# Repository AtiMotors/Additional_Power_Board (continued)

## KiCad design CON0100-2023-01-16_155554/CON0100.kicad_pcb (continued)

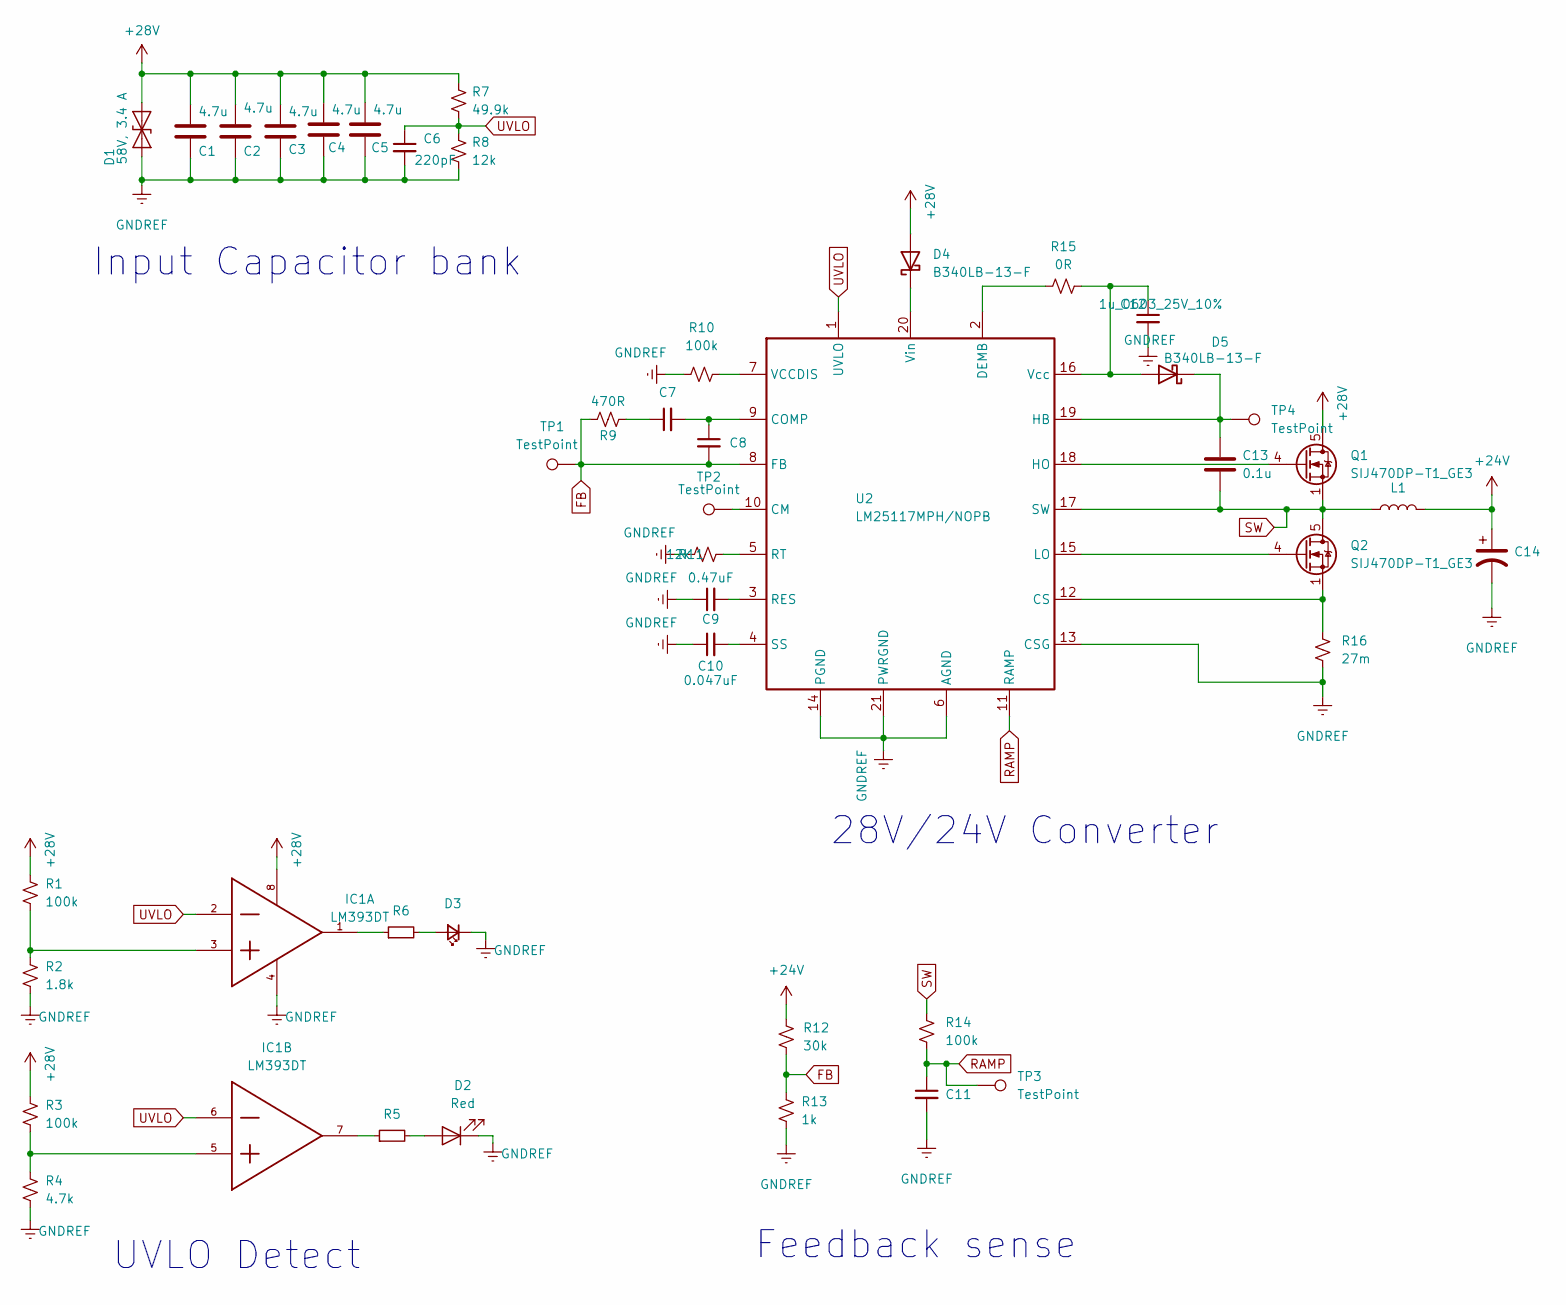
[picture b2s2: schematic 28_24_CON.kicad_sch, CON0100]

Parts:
C1, C2, C3, C4, C5: C_4.7u_1206_CL31B475KAHNNNE; R_1206_3216Metric_Pad1.42x1.75mm_HandSolder; MPN CL31B475KAHNNNE
C6: C_0603_220pF_50V_ECJ-1VC1H221J; C_0603_1608Metric_Pad1.08x0.95mm_HandSolder; MPN ECJ-1VC1H221J
C7: C_0.01uf_0603_50V_ECJ-1VB1H103K; C_0603_1608Metric_Pad1.08x0.95mm_HandSolder; MPN ECJ-1VB1H103K
C8: C_10pF_0603_GCM1885C1H100JA16D; C_0603_1608Metric_Pad1.08x0.95mm_HandSolder; MPN GCM1885C1H100JA16D
C9: C_0603_0.47uF_25V_CGA3E3X7R1E474K080AB; C_0603_1608Metric_Pad1.08x0.95mm_HandSolder; MPN CGA3E3X7R1E474K080AB
C10: C_0603_0.047uF_16V_10%_ECJ-1VB1C473K; C_0603_1608Metric_Pad1.08x0.95mm_HandSolder; MPN ECJ-1VB1C473K
C11: C_820pF_0603_50V_GCM1885C1H821JA16D; C_0603_1608Metric_Pad1.08x0.95mm_HandSolder; MPN GCM1885C1H821JA16D
C12: C_1uf_0603_GCJ188R71E105KA01D; C_0603_1608Metric_Pad1.08x0.95mm_HandSolder; MPN GCJ188R71E105KA01D
C13: C_0603_0.1u_50V_C0603C104K5RACAUTO; C_0603_1608Metric_Pad1.05x0.95mm_HandSolder; Voltage 50V; MPN C0603C104K5RACAUTO
C14: C_0.22uF_RAD_50V_20%; C_Elec_4x5.4; MPN UWP1HR22MCL1GB
D1: D_TVS_40V_ATV02W360B-HF; D_SOD-123F; MPN ATV02W360B-HF
D2: D_LED_0603_Red_150060RS75000; R_0603_1608Metric_Pad1.05x0.95mm_HandSolder; MPN 150060RS75000
D3: D_LED_0603_Green_150060GS75000; LED_0603_1608Metric_Pad1.05x0.95mm_HandSolder; MPN 150060GS75000
D4, D5: B340LB-13-F; D_SMC
IC1: LM393DT; SOIC8; MPN LM393DT
L1: L_22uH_12A_37mOhms_SMD_12.5mmx13.5mm; L_Bourns_SRP1245A; MPN SRP1265A-220M
Q1, Q2: SIJ470DP-T1_GE3; PowerPAK_SO-8_Single; MPN SIJ470DP-T1_GE3
R1, R3, R10: R_100k_0603_1/10W_CRGP0603F100K; R_0603_1608Metric_Pad0.98x0.95mm_HandSolder; MPN ERJ-3EKF1003V
R2: R_1.8k_0603_ERJ-3EKF1801V; R_0603_1608Metric_Pad0.98x0.95mm_HandSolder; MPN ERJ-3EKF1801V
R4: R_4.7k_0603_ERJ-3GEYJ472V; R_0603_1608Metric_Pad0.98x0.95mm_HandSolder; MPN ERJ-3GEYJ472V
R5, R6: R_3.3k_0603_ERJ-PA3F3301V; R_0603_1608Metric_Pad0.98x0.95mm_HandSolder; MPN ERJ-PA3F3301V
R7: R_49.9k_0603_ERJ3EKF4992V; R_0603_1608Metric_Pad0.98x0.95mm_HandSolder; MPN ERJ-3EKF4992V
R8, R11: R_12k_0603_ERJ3EKF1202V; R_0603_1608Metric_Pad0.98x0.95mm_HandSolder; MPN ERJ-3EKF1202V
R9: R_470R_0603_ERJ-3EKF4700V; R_0603_1608Metric_Pad0.98x0.95mm_HandSolder; MPN ERJ-3EKF4700V
R12: R_30k_0603_ERJ-PB3B3002V; R_0603_1608Metric_Pad0.98x0.95mm_HandSolder; MPN ERJ-PB6B3002V
R13: R_1k_0603_ERJ-3EKF1001V; R_0603_1608Metric_Pad0.98x0.95mm_HandSolder; MPN 3EKF1001V
R14: R_100k_0603_0.1%_ERA3APB104V; R_0603_1608Metric_Pad1.05x0.95mm_HandSolder; MPN ERA3APB104V
R15: R_0R_0603_ERJ-3GEY0R00V; R_0603_1608Metric_Pad0.98x0.95mm_HandSolder; MPN ERJ-3GEY0R00V
R16: R_27mOhms_0805_ERJ-6BWFR027V; R_0805_2012Metric_Pad1.20x1.40mm_HandSolder; MPN ERJ-6BWFR027V
TP1, TP2, TP3, TP4: TestPoint; TestPoint_Pad_D1.0mm
U2: LM25117MPH/NOPB; SOP65P640X110-21N

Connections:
+24V: C14.1, L1.2, R12.1; also elsewhere on the board
+28V: C1.1, C2.1, C3.1, C4.1, C5.1, D1.2 (A2), D4.2 (A), IC1.8, Q1.5 (D), R1.1, R3.1, R7.1; also elsewhere on the board
FB: C8.2, R9.1, R12.2, R13.1, TP1.1, U2.8 (FB)
GNDREF: C1.2, C2.2, C3.2, C4.2, C5.2, C6.2, C9.1, C10.1, C11.2, C12.2, C14.2, D1.1 (A1), D2.1 (K), D3.1 (K), IC1.4, R2.2, R4.2, R8.2, R10.1, R11.1, R13.2, R16.2, U2.6 (AGND), U2.13 (CSG), U2.14 (PGND), U2.21 (PWRGND); also elsewhere on the board
unnamed: C7.1, R9.2
unnamed: C7.2, C8.1, U2.9 (COMP)
unnamed: C9.2, U2.3 (RES)
unnamed: C10.2, U2.4 (SS)
unnamed: C13.1, D5.1 (K), TP4.1, U2.19 (HB)
unnamed: D2.2 (A), R5.2
unnamed: D3.2 (A), R6.2
unnamed: D4.1 (K), U2.20 (Vin)
unnamed: C12.1, D5.2 (A), R15.2, U2.16 (Vcc)
unnamed: IC1.1, R6.1
unnamed: IC1.3, R1.2, R2.1
unnamed: IC1.5, R3.2, R4.1
unnamed: IC1.7, R5.1
unnamed: Q2.1 (S), Q2.2 (S), Q2.3 (S), R16.1, U2.12 (CS)
unnamed: R10.2, U2.7 (VCCDIS)
unnamed: R11.2, U2.5 (RT)
unnamed: R15.1, U2.2 (DEMB)
unnamed: TP2.1, U2.10 (CM)
unnamed: Q2.4 (G), U2.15 (LO)
unnamed: Q1.4 (G), U2.18 (HO)
RAMP: C11.1, R14.2, TP3.1, U2.11 (RAMP)
SW: C13.2, L1.1, Q1.1 (S), Q1.2 (S), Q1.3 (S), Q2.5 (D), R14.1, U2.17 (SW)
UVLO: C6.1, IC1.2, IC1.6, R7.2, R8.1, U2.1 (UVLO)

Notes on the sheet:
UVLO Detect
Feedback sense
28V/24V Converter
Input Capacitor bank

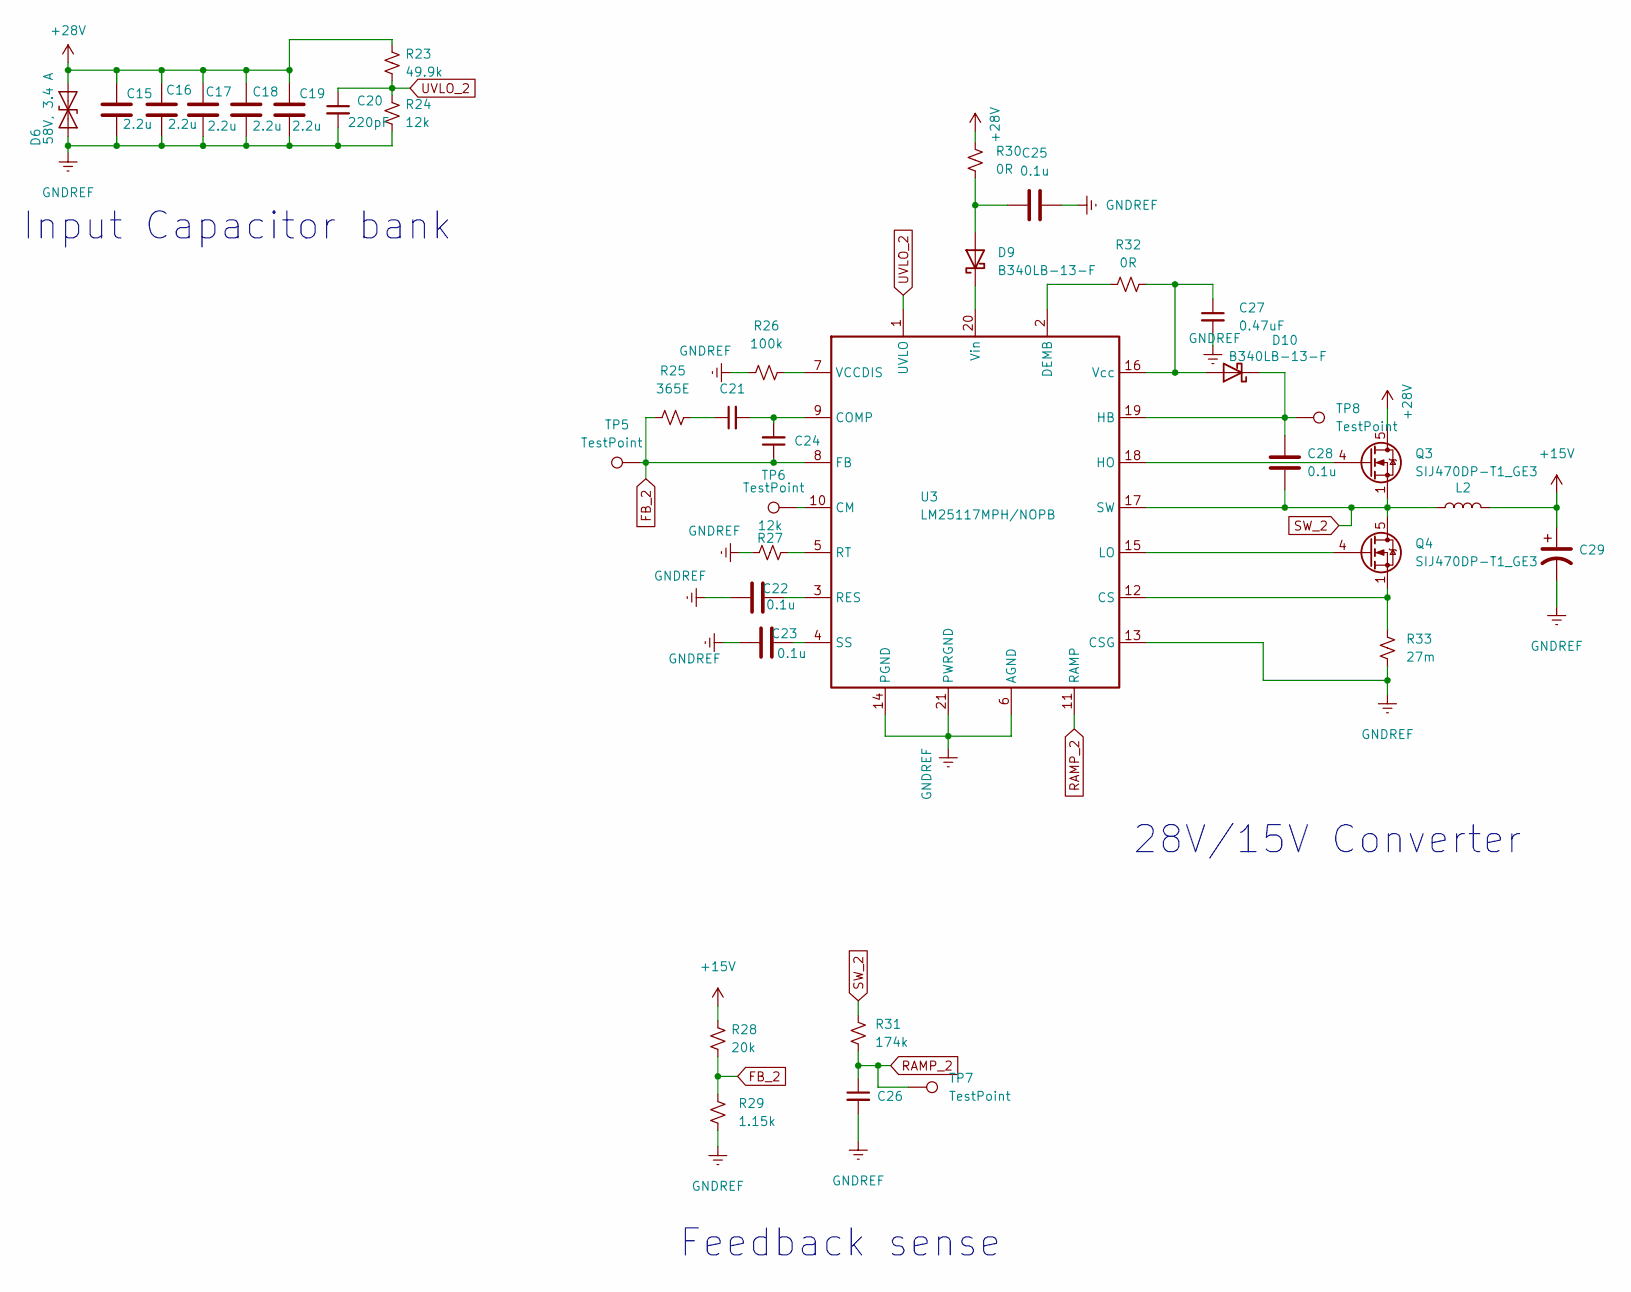
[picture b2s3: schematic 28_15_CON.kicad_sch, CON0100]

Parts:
C15, C16, C17, C19: C_2.2u_1210_C1210F225K5RACAUTO; C_1210_3225Metric_Pad1.33x2.70mm_HandSolder; MPN C1210F225K5RACAUTO
C18: C_1210_3225Metric_Pad1.33x2.70mm_HandSolder; MPN C1210F225K5RACAUTO
C20: C_0603_220pF_50V_ECJ-1VC1H221J; C_0603_1608Metric_Pad1.08x0.95mm_HandSolder; MPN ECJ-1VC1H221J
C21: C_4700pF_0805_CL21C472JAFNNNE; C_0805_2012Metric_Pad1.18x1.45mm_HandSolder; MPN CL21C472JAFNNNE
C22, C23, C25, C28: C_0603_0.1u_50V_C0603C104K5RACAUTO; C_0603_1608Metric_Pad1.05x0.95mm_HandSolder; Voltage 50V; MPN C0603C104K5RACAUTO
C24: C_150pF_0805_08055A151J4T4A; C_0805_2012Metric_Pad1.18x1.45mm_HandSolder; MPN 08055A151J4T4A
C26: C_820pF_0603_50V_GCM1885C1H821JA16D; C_0603_1608Metric_Pad1.08x0.95mm_HandSolder; MPN GCM1885C1H821JA16D
C27: C_0603_0.47uF_25V_CGA3E3X7R1E474K080AB; C_0603_1608Metric_Pad1.08x0.95mm_HandSolder; MPN CGA3E3X7R1E474K080AB
C29: C_0.22uF_RAD_50V_20%; C_Elec_4x5.4; MPN UWP1HR22MCL1GB
D6: D_TVS_40V_ATV02W360B-HF; D_SOD-123F; MPN ATV02W360B-HF
D9, D10: B340LB-13-F; D_SMC
L2: L_33uH_3A_60mOhms_SMD_12.5mmx12.5mm; L_Bourns_SRR1260; MPN SRR1260-330M
Q3, Q4: SIJ470DP-T1_GE3; PowerPAK_SO-8_Single; MPN SIJ470DP-T1_GE3
R23: MPN ERJ-3EKF4992V
R24, R27: R_12k_0603_ERJ3EKF1202V; R_0603_1608Metric_Pad0.98x0.95mm_HandSolder; MPN ERJ-3EKF1202V
R25: R_365R_0603_ERA-3AEB3650V; R_0603_1608Metric_Pad0.98x0.95mm_HandSolder; MPN 3AEB3650V
R26: R_100k_0603_1/10W_CRGP0603F100K; R_0603_1608Metric_Pad0.98x0.95mm_HandSolder; MPN ERJ-3EKF1003V
R28: R_20k_0603_ERJ-3EKF2002V; R_0603_1608Metric_Pad0.98x0.95mm_HandSolder; MPN ERJ-3EKF2002V
R29: R_1.15k_0603_ERJ-3EKF1151V; R_0603_1608Metric_Pad0.98x0.95mm_HandSolder; MPN ERJ-3EKF1151V
R30, R32: R_0R_0603_ERJ-3GEY0R00V; R_0603_1608Metric_Pad0.98x0.95mm_HandSolder; MPN ERJ-3GEY0R00V
R31: R_174k_0603_ERJ-3EKF1743V; R_0603_1608Metric_Pad0.98x0.95mm_HandSolder; MPN ERJ-3EKF1743V
R33: R_27mOhms_0805_ERJ-6BWFR027V; R_0805_2012Metric_Pad1.20x1.40mm_HandSolder; MPN ERJ-6BWFR027V
TP5, TP6, TP7, TP8: TestPoint; TestPoint_Pad_D1.0mm
U3: LM25117MPH/NOPB; SOP65P640X110-21N

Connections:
+15V: C29.1, L2.2, R28.1; also elsewhere on the board
+28V: C15.1, C16.1, C17.1, C18.1, C19.1, D6.2 (A2), Q3.5 (D), R23.1, R30.2; also elsewhere on the board
FB_2: C24.1, R25.1, R28.2, R29.1, TP5.1, U3.8 (FB)
GNDREF: C15.2, C16.2, C17.2, C18.2, C19.2, C20.2, C22.1, C23.1, C25.2, C26.2, C27.2, C29.2, D6.1 (A1), R24.2, R26.1, R27.1, R29.2, R33.2, U3.6 (AGND), U3.13 (CSG), U3.14 (PGND), U3.21 (PWRGND); also elsewhere on the board
unnamed: C21.1, R25.2
unnamed: C21.2, C24.2, U3.9 (COMP)
unnamed: C22.2, U3.3 (RES)
unnamed: C23.2, U3.4 (SS)
unnamed: C25.1, D9.2 (A), R30.1
unnamed: C27.1, D10.2 (A), R32.2, U3.16 (Vcc)
unnamed: C28.1, D10.1 (K), TP8.1, U3.19 (HB)
unnamed: D9.1 (K), U3.20 (Vin)
unnamed: Q3.4 (G), U3.18 (HO)
unnamed: Q4.1 (S), Q4.2 (S), Q4.3 (S), R33.1, U3.12 (CS)
unnamed: Q4.4 (G), U3.15 (LO)
unnamed: R26.2, U3.7 (VCCDIS)
unnamed: R27.2, U3.5 (RT)
unnamed: R32.1, U3.2 (DEMB)
unnamed: TP6.1, U3.10 (CM)
RAMP_2: C26.1, R31.2, TP7.1, U3.11 (RAMP)
SW_2: C28.2, L2.1, Q3.1 (S), Q3.2 (S), Q3.3 (S), Q4.5 (D), R31.1, U3.17 (SW)
UVLO_2: C20.1, R23.2, R24.1, U3.1 (UVLO); also elsewhere on the board

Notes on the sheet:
28V/15V Converter
Feedback sense
Input Capacitor bank

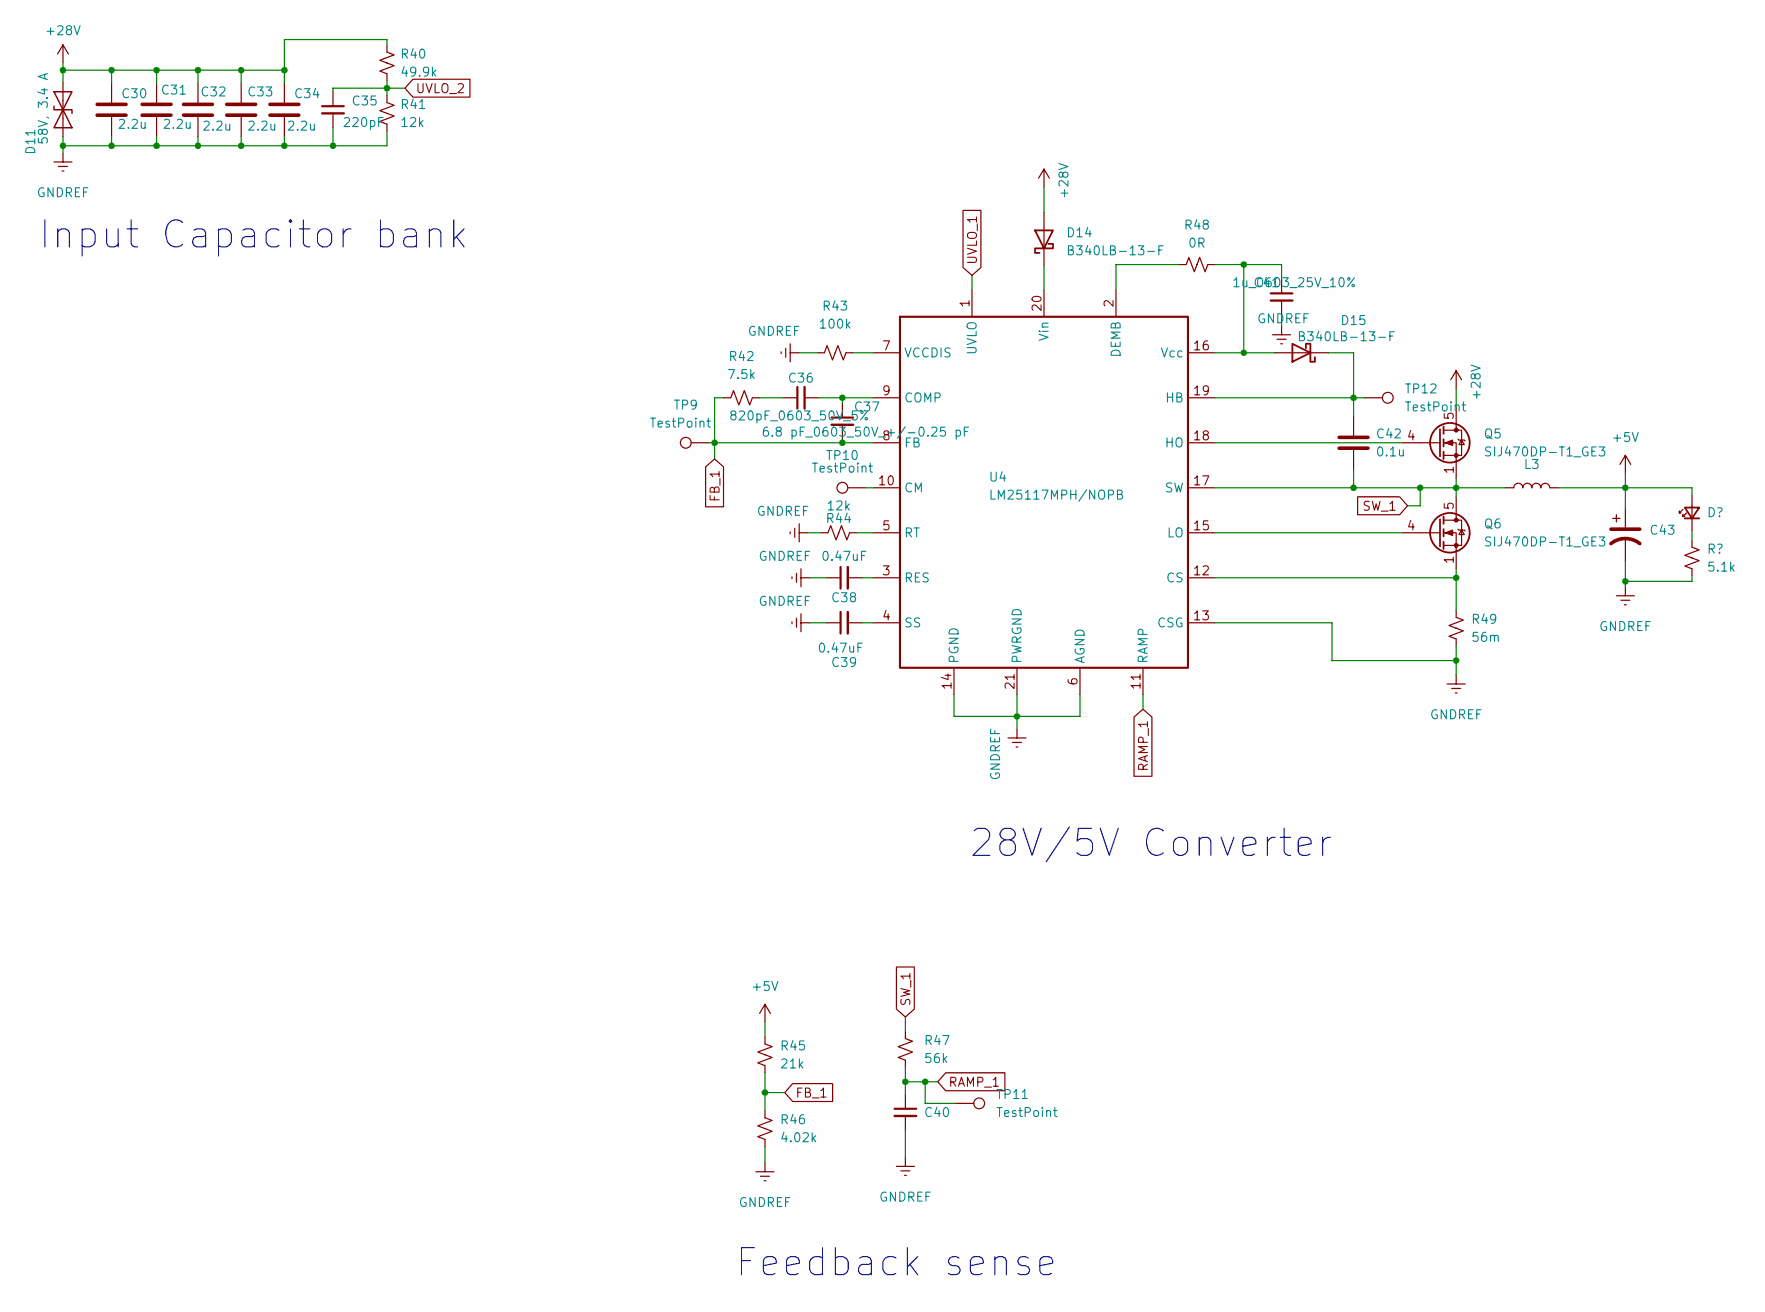
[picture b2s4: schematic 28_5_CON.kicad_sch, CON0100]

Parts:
C30, C31, C32, C33, C34: C_2.2u_1210_C1210F225K5RACAUTO; C_1210_3225Metric_Pad1.33x2.70mm_HandSolder; MPN C1210F225K5RACAUTO
C35: C_0603_220pF_50V_ECJ-1VC1H221J; C_0603_1608Metric_Pad1.08x0.95mm_HandSolder; MPN ECJ-1VC1H221J
C36, C40: C_820pF_0603_50V_GCM1885C1H821JA16D; C_0603_1608Metric_Pad1.08x0.95mm_HandSolder; MPN GCM1885C1H821JA16D
C37: C_6.8pF_0603_CL10C6R8CB8NNNC; C_0603_1608Metric_Pad1.08x0.95mm_HandSolder; MPN CL10C6R8CB8NNNC
C38, C39: C_0603_0.47uF_25V_CGA3E3X7R1E474K080AB; C_0603_1608Metric_Pad1.08x0.95mm_HandSolder; MPN CGA3E3X7R1E474K080AB
C41: C_1uf_0603_GCJ188R71E105KA01D; C_0603_1608Metric_Pad1.08x0.95mm_HandSolder; MPN GCJ188R71E105KA01D
C42: C_0603_0.1u_50V_C0603C104K5RACAUTO; C_0603_1608Metric_Pad1.05x0.95mm_HandSolder; Voltage 50V; MPN C0603C104K5RACAUTO
C43: C_3.3uF_RAD_50V_20%; C_Elec_4x5.8; MPN UUD1H3R3MCL1GS
D11: D_TVS_40V_ATV02W360B-HF; D_SOD-123F; MPN ATV02W360B-HF
D14, D15: B340LB-13-F; D_SMC
L3: L_27uH_5A_40mOhms_SMD_12.0mmx12.0mm; L_Bourns_SRR1210A; MPN SRR1210A-270M
Q5, Q6: SIJ470DP-T1_GE3; PowerPAK_SO-8_Single; MPN SIJ470DP-T1_GE3
R40: R_49.9k_0603_ERJ3EKF4992V; R_0603_1608Metric_Pad0.98x0.95mm_HandSolder; MPN ERJ-3EKF4992V
R41, R44: R_12k_0603_ERJ3EKF1202V; R_0603_1608Metric_Pad0.98x0.95mm_HandSolder; MPN ERJ-3EKF1202V
R42: R_7.5k_0603_ERA-3APB752V; R_0603_1608Metric_Pad0.98x0.95mm_HandSolder; MPN ERA-3APB752V
R43: R_100k_0603_1/10W_CRGP0603F100K; R_0603_1608Metric_Pad0.98x0.95mm_HandSolder; MPN ERJ-3EKF1003V
R45: R_21k_0603_RT0603BRD0721KL; R_0603_1608Metric_Pad0.98x0.95mm_HandSolder; MPN RT0603BRD0721KL
R46: R_4.02k_0603_RG1608P-4021-B-T5; R_0603_1608Metric_Pad0.98x0.95mm_HandSolder; MPN RG1608P-4021-B-T5
R47: R_56k_0603_ERJ-3EKF5602V; R_0603_1608Metric_Pad0.98x0.95mm_HandSolder; MPN ERJ-3EKF5602V
R48: R_0R_0603_ERJ-3GEY0R00V; R_0603_1608Metric_Pad0.98x0.95mm_HandSolder; MPN ERJ-3GEY0R00V
R49: R_56mOhms_0805_ERJ-6BWFR056V; R_0805_2012Metric_Pad1.20x1.40mm_HandSolder; MPN ERJ-6BWFR056V
TP9, TP10, TP11, TP12: TestPoint; TestPoint_Pad_D1.0mm
U4: LM25117MPH/NOPB; SOP65P640X110-21N

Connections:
+5V: C43.1, L3.2, R45.1; also elsewhere on the board
+28V: C30.1, C31.1, C32.1, C33.1, C34.1, D11.2 (A2), D14.2 (A), Q5.5 (D), R40.1; also elsewhere on the board
FB_1: C37.2, R42.1, R45.2, R46.1, TP9.1, U4.8 (FB)
GNDREF: C30.2, C31.2, C32.2, C33.2, C34.2, C35.2, C38.1, C39.1, C40.2, C41.2, C43.2, D11.1 (A1), R41.2, R43.1, R44.1, R46.2, R49.2, U4.6 (AGND), U4.13 (CSG), U4.14 (PGND), U4.21 (PWRGND); also elsewhere on the board
unnamed: C36.1, R42.2
unnamed: C36.2, C37.1, U4.9 (COMP)
unnamed: C38.2, U4.3 (RES)
unnamed: C39.2, U4.4 (SS)
unnamed: C41.1, D15.2 (A), R48.2, U4.16 (Vcc)
unnamed: C42.1, D15.1 (K), TP12.1, U4.19 (HB)
unnamed: D14.1 (K), U4.20 (Vin)
unnamed: Q5.4 (G), U4.18 (HO)
unnamed: Q6.1 (S), Q6.2 (S), Q6.3 (S), R49.1, U4.12 (CS)
unnamed: Q6.4 (G), U4.15 (LO)
unnamed: R43.2, U4.7 (VCCDIS)
unnamed: R44.2, U4.5 (RT)
unnamed: R48.1, U4.2 (DEMB)
unnamed: TP10.1, U4.10 (CM)
RAMP_1: C40.1, R47.2, TP11.1, U4.11 (RAMP)
SW_1: C42.2, L3.1, Q5.1 (S), Q5.2 (S), Q5.3 (S), Q6.5 (D), R47.1, U4.17 (SW)
UVLO_1: U4.1 (UVLO); also elsewhere on the board
UVLO_2: C35.1, R40.2, R41.1; also elsewhere on the board

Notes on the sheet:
Feedback sense
28V/5V Converter
Input Capacitor bank

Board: 2 copper layers, 143 parts (0 on the bottom side), 78 nets, no tracks yet.

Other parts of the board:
D7, D12: D_LED_0603_Red_150060RS75000; LED_0603_1608Metric_Pad1.05x0.95mm_HandSolder
D8, D13: D_LED_0603_Green_150060GS75000; LED_0603_1608Metric_Pad1.05x0.95mm_HandSolder
IC2, IC3: LM393DT; SOIC8
R17, R19, R34, R36: R_100k_0603_1/10W_CRGP0603F100K; R_0603_1608Metric_Pad0.98x0.95mm_HandSolder
R18, R35: R_1.8k_0603_ERJ-3EKF1801V; R_0603_1608Metric_Pad0.98x0.95mm_HandSolder
R20, R37: R_4.7k_0603_ERJ-3GEYJ472V; R_0603_1608Metric_Pad0.98x0.95mm_HandSolder
R21, R22, R38, R39: R_3.3k_0603_ERJ-PA3F3301V; R_0603_1608Metric_Pad0.98x0.95mm_HandSolder

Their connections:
+28V: IC2.8, IC3.8, R17.1, R19.1, R34.1, R36.1; also elsewhere on the board
GNDREF: D7.1 (K), D8.1 (K), D12.1 (K), D13.1 (K), IC2.4, IC3.4, R18.2, R20.2, R35.2, R37.2; also elsewhere on the board
unnamed: D7.2 (A), R21.2
unnamed: D8.2 (A), R22.2
unnamed: D12.2 (A), R38.2
unnamed: D13.2 (A), R39.2
unnamed: IC2.1, R22.1
unnamed: IC2.3, R17.2, R18.1
unnamed: IC2.5, R19.2, R20.1
unnamed: IC2.7, R21.1
unnamed: IC3.1, R39.1
unnamed: IC3.3, R34.2, R35.1
unnamed: IC3.5, R36.2, R37.1
unnamed: IC3.7, R38.1
UVLO_1: IC3.2, IC3.6; also elsewhere on the board
UVLO_2: IC2.2, IC2.6; also elsewhere on the board

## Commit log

2023-02-06 CON0100 rev01
    Additional Power Board design Files
    1. Hierarchal schematic
    2. 28/24 V Converter Design
    3. 28/15 V Converter Design
    4. 28/5 V Converter Design
    In addition with PCB design.
2023-02-07 Added datasheets
    Datasheets of Schottky diode and Reverse polarity Mosfet
2023-03-02 Silk screen updated as per PC process request
    Silkscreen changed to 25 mm width and 35 mm height for manufacturing restraints.
